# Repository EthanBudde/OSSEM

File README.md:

# OSSEM
OSSEM organization repo

Espresso brewing is a thermo-fluid process where temperature, pressure, flow rate, and time directly effect extraction and flavor. Commercial smart espresso machines offer advanced control, but are expensive, closed-source, and difficult to adapt for experimental research. Existing open-source modifications improve accessibility but do not fully support research-grade measurement or instrumentation. 

This project focuses on building an open-source smart emissions monitor based on the Gaggia Classic Pro, using platforms such as Gaggiuino and Gaggia Mate for embedded control and data logging. The system will allow precise control of brewing parameters, including temperature, pressure, flow profiling, and shot timing. 

Working with the Healthy Buildings Research Lab and the Coffee Telesensing Lab at Portland State University, the machine will be adapted to support PTR-MS and UV-VIS spectroscopy for measuring volatile organic compounds (VOCs) released during espresso extraction. The result will be a flexible, open source platform that supports repeatable espresso brewing and controlled emissions research.

<p align="center">
  <em>Smart Emissions Monitor – Emissions Control Unit (ECU Final Product)</em>
</p>

<p align="center">
  <em>Emissions Control Unit Sensors</em>
</p>

<p align="center">
  <em>Smart Emissions Monitor – Emissions Control Unit (ECU Prototype)</em>
</p>

<p align="center">
  <em>Smart Emissions Monitor – Block Diagram</em>
</p>

<p align="center">
  <em>Smart Emissions Monitor – Schematic v1.8.2</em>
</p>

<p align="center">
  <em>Smart Emissions Monitor – PCB v1.8.2 </em>
</p>

<p align="center">
  <em>Smart Emissions Monitor – 3D PCB v1.8 Front</em>
</p>

<p align="center">
  <em>Smart Emissions Monitor – 3D PCB v1.8 Back</em>
</p>

<p align="center">
  <em>Smart Emissions Monitor – PCB v1.8 front</em>
</p>

<p align="center">
  <em>Smart Emissions Monitor – PCB v1.8 back</em>
</p>

<p align="center">
  <em>Smart Emissions Monitor – PCB v1.8 back with dimensions</em>
</p>

## Acknowledgments
This project builds on:
- Gaggiuino (open-source espresso control system)
- Adafruit sensor libraries
- KiCad component libraries

PCB renders generated using OSH Park

All third-party resources are used in accordance with their respective licenses.

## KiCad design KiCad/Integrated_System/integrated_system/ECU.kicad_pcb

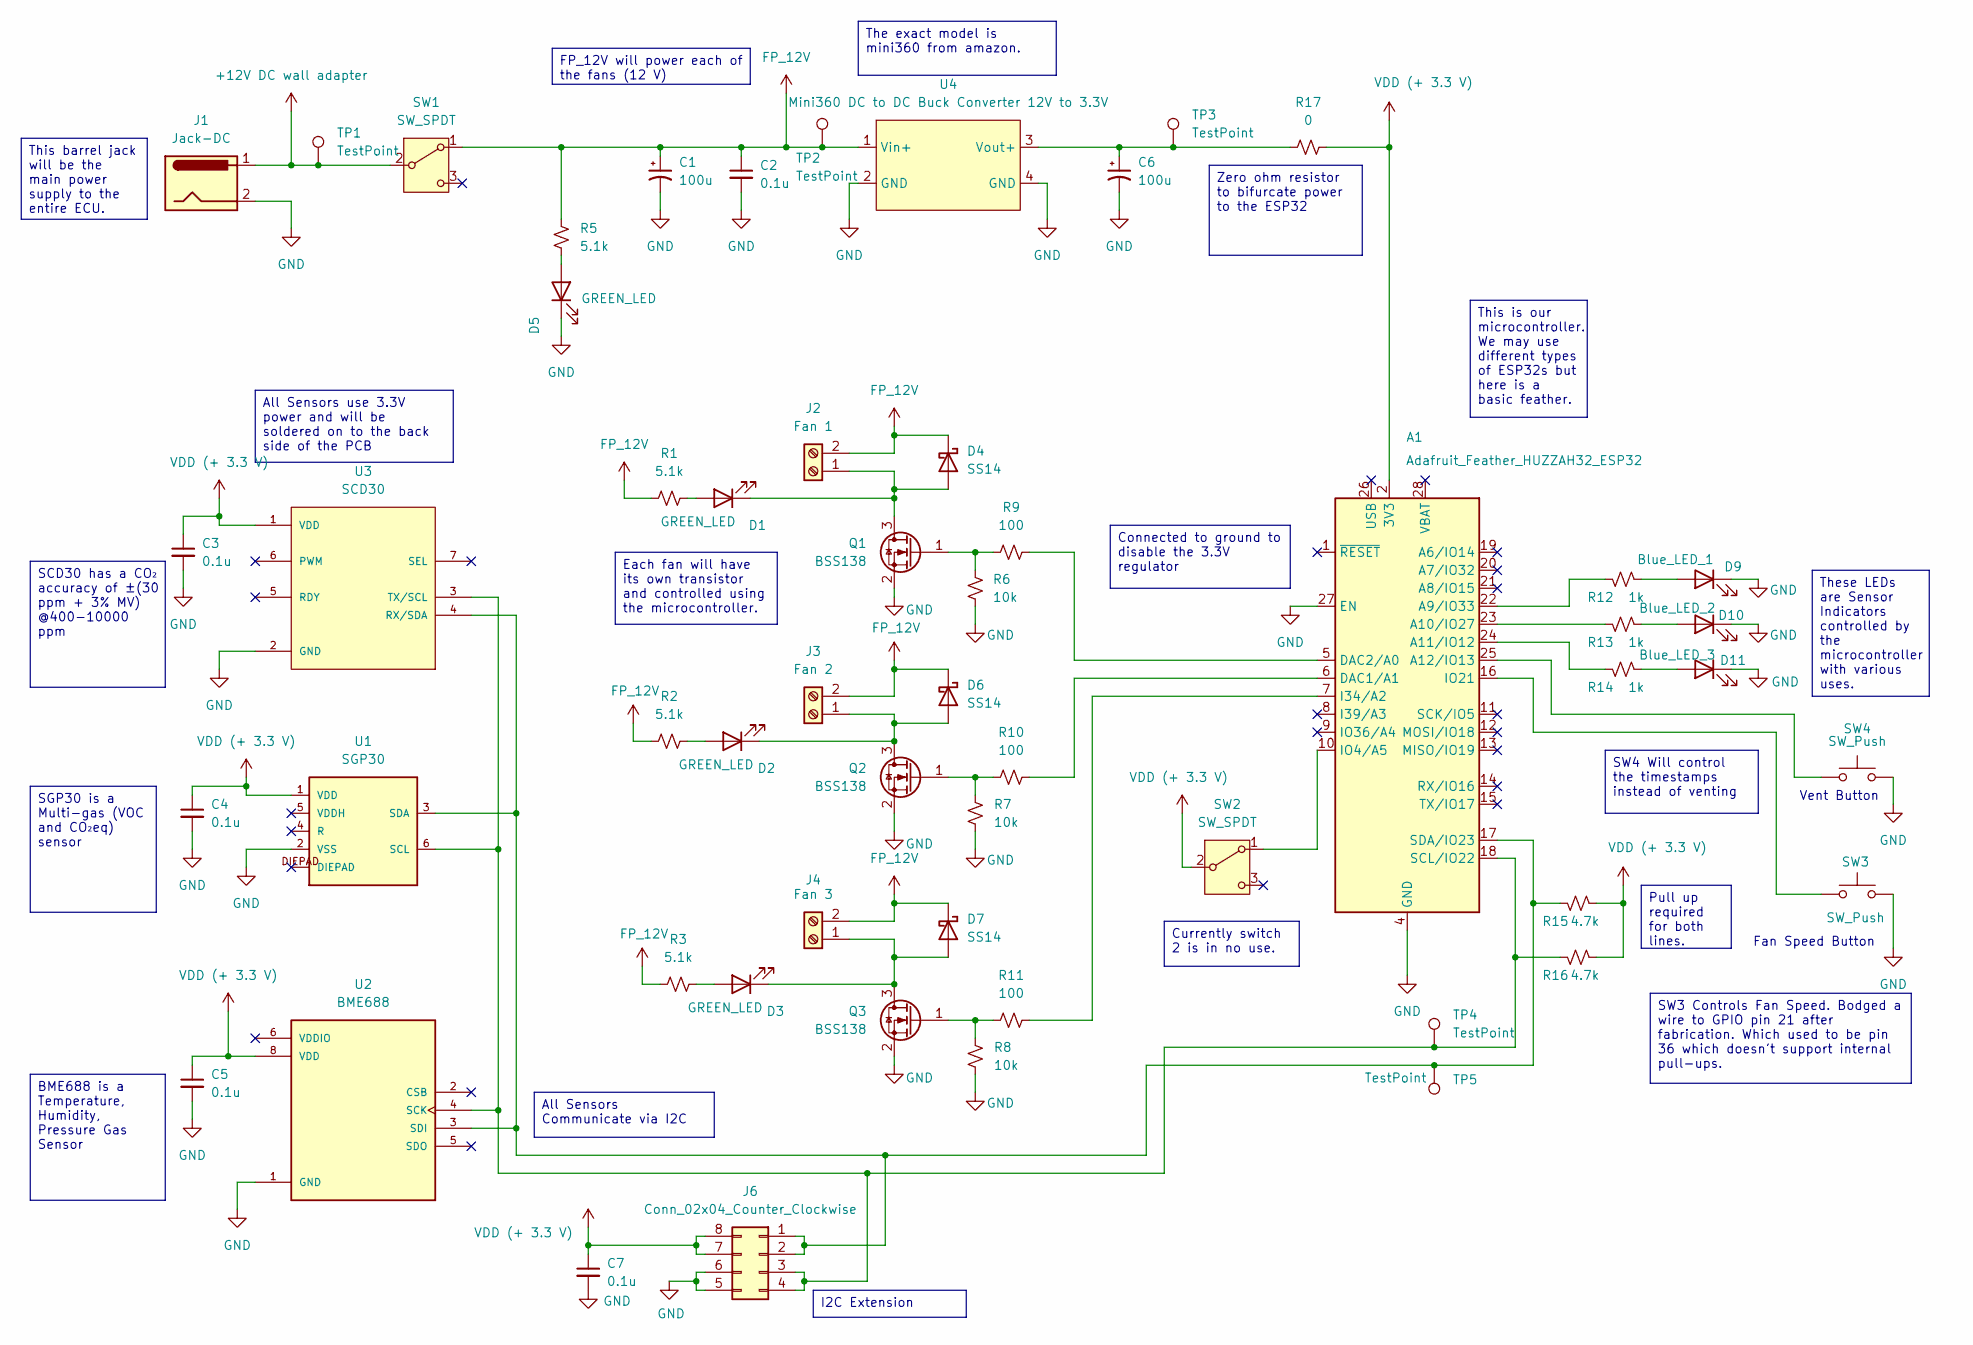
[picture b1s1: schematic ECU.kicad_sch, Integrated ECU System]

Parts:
A1: Adafruit_Feather_HUZZAH32_ESP32; Adafruit_Feather
C1, C6: 100u; CP_Elec_6.3x7.7
C2, C3, C4, C5, C7: 0.1u; C_1206_3216Metric_Pad1.33x1.80mm_HandSolder
D1, D2, D3, D5: GREEN_LED; LED_1206_3216Metric_Pad1.42x1.75mm_HandSolder
D4, D6, D7: SS14; D_SMA
D9: Blue_LED_1; LED_1206_3216Metric_Pad1.42x1.75mm_HandSolder
D10: Blue_LED_2; LED_1206_3216Metric_Pad1.42x1.75mm_HandSolder
D11: Blue_LED_3; LED_1206_3216Metric_Pad1.42x1.75mm_HandSolder
J1: Jack-DC; BarrelJack_GCT_DCJ200-10-A_Horizontal
J2: Fan 1; TerminalBlock_Phoenix_MKDS-1,5-2-5.08_1x02_P5.08mm_Horizont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
J3: Fan 2; TerminalBlock_Phoenix_MKDS-1,5-2-5.08_1x02_P5.08mm_Horizont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
J4: Fan 3; TerminalBlock_Phoenix_MKDS-1,5-2-5.08_1x02_P5.08mm_Horizont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
J6: Conn_02x04_Counter_Clockwise; PinSocket_2x04_P2.54mm_Vertical
Q1, Q2, Q3: BSS138; SOT-23_Handsoldering
R1, R2, R3, R5: 5.1k; R_1206_3216Metric_Pad1.30x1.75mm_HandSolder
R6, R7, R8: 10k; R_1206_3216Metric_Pad1.30x1.75mm_HandSolder
R9, R10, R11: 100; R_1206_3216Metric_Pad1.30x1.75mm_HandSolder
R12, R13, R14: 1k; R_1206_3216Metric_Pad1.30x1.75mm_HandSolder
R15, R16: 4.7k; R_1206_3216Metric_Pad1.30x1.75mm_HandSolder
R17: 0; R_1206_3216Metric_Pad1.30x1.75mm_HandSolder
SW1, SW2: SW_SPDT; switch_dm
SW3, SW4: SW_Push; SW_PUSH_6mm
TP1, TP2, TP3, TP4, TP5: TestPoint; Pin_D0.7mm_L6.5mm_W1.8mm_FlatFork
U1: SGP30
U2: BME688; PSON80P300X300X100-8N; PARTREV 1.9
U3: SCD30; MODULE_SCD30; PARTREV D1
U4: Mini360 DC to DC Buck Converter 12V to 3.3V; Mini360

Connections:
+12V DC wall adapter: J1.1, SW1.2 (B), TP1.1
FP_12V: C1.1, C2.1, D4.1 (K), D6.1 (K), D7.1 (K), J2.2, J3.2, J4.2, R1.1, R2.1, R3.1, R5.2, SW1.1 (A), TP2.1, U4.1 (Vin+)
GND: A1.4 (GND), A1.27 (EN), C1.2, C2.2, C3.2, C4.2, C5.2, C6.2, C7.2, D5.1 (K), D9.1 (K), D10.1 (K), D11.1 (K), J1.2, J6.5, J6.6, Q1.2 (S), Q2.2 (S), Q3.2 (S), R6.1, R7.1, R8.1, SW3.1, SW4.1, U1.2 (VSS), U2.1 (GND), U2.7 (GND), U3.2 (GND), U4.2 (GND), U4.4 (GND)
unnamed: A1.22 (A9/IO33), R12.2
unnamed: A1.23 (A10/IO27), R13.2
unnamed: A1.24 (A11/IO12), R14.2
unnamed: A1.25 (A12/IO13), SW4.2
unnamed: A1.6 (DAC1/A1), R10.2
unnamed: A1.5 (DAC2/A0), R9.2
unnamed: A1.7 (I34/A2), R11.2
unnamed: A1.10 (IO4/A5), SW2.1 (A)
unnamed: A1.16 (IO21), SW3.2
unnamed: A1.18 (SCL/IO22), J6.3, J6.4, R16.2, TP4.1, U1.6 (SCL), U2.4 (SCK), U3.3 (TX/SCL)
unnamed: A1.17 (SDA/IO23), J6.1, J6.2, R15.2, TP5.1, U1.3 (SDA), U2.3 (SDI), U3.4 (RX/SDA)
unnamed: D1.2 (A), R1.2
unnamed: D1.1 (K), D4.2 (A), J2.1, Q1.3 (D)
unnamed: D2.2 (A), R2.2
unnamed: D2.1 (K), D6.2 (A), J3.1, Q2.3 (D)
unnamed: D3.2 (A), R3.2
unnamed: D3.1 (K), D7.2 (A), J4.1, Q3.3 (D)
unnamed: D5.2 (A), R5.1
unnamed: D9.2 (A), R12.1
unnamed: D10.2 (A), R13.1
unnamed: D11.2 (A), R14.1
unnamed: Q1.1 (G), R6.2, R9.1
unnamed: Q2.1 (G), R7.2, R10.1
unnamed: Q3.1 (G), R8.2, R11.1
unnamed: C6.1, R17.1, TP3.1, U4.3 (Vout+)
VDD (+ 3.3 V): A1.2 (3V3), C3.1, C4.1, C5.1, C7.1, J6.7, J6.8, R15.1, R16.1, R17.2, SW2.2 (B), U1.1 (VDD), U2.8 (VDD), U3.1 (VDD)

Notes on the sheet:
Vent Button
Fan Speed Button
These LEDs are Sensor Indicators controlled by the microcontroller with various uses.
Each fan will have its own transistor and controlled using the microcontroller.
Connected to ground to disable the 3.3V regulator
BME688 is a Temperature, Humidity, Pressure Gas Sensor
I2C Extension
SGP30 is a Multi-gas (VOC and CO₂eq) sensor
SW3 Controls Fan Speed. Bodged a wire to GPIO pin 21 after fabrication. Which used to be pin 36 which doesn't support internal pull-ups.
FP_12V will power each of the fans (12 V)
Zero ohm resistor to bifurcate power to the ESP32
The exact model is mini360 from amazon.
All Sensors use 3.3V power and will be soldered on to the back side of the PCB
All Sensors Communicate via I2C
SCD30 has a CO₂ accuracy of ±(30 ppm + 3% MV) @400-10000 ppm
This barrel jack will be the main power supply to the entire ECU.
This is our microcontroller. We may use different types of ESP32s but here is a basic feather.
Currently switch 2 is in no use.
SW4 Will control the timestamps instead of venting
Pull up required for both lines.

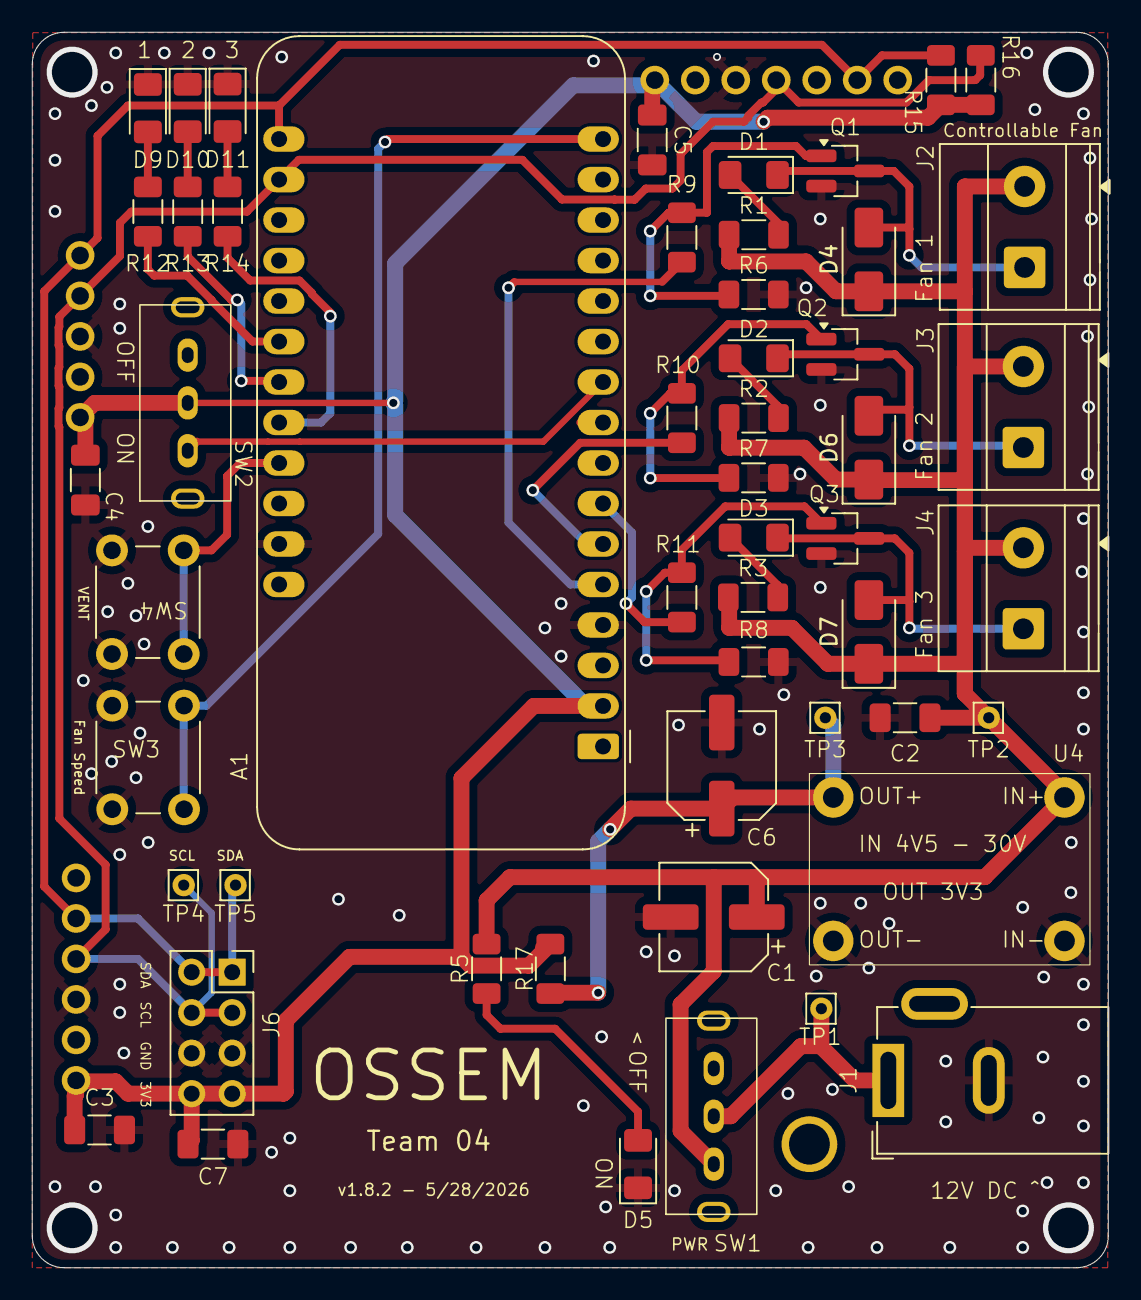
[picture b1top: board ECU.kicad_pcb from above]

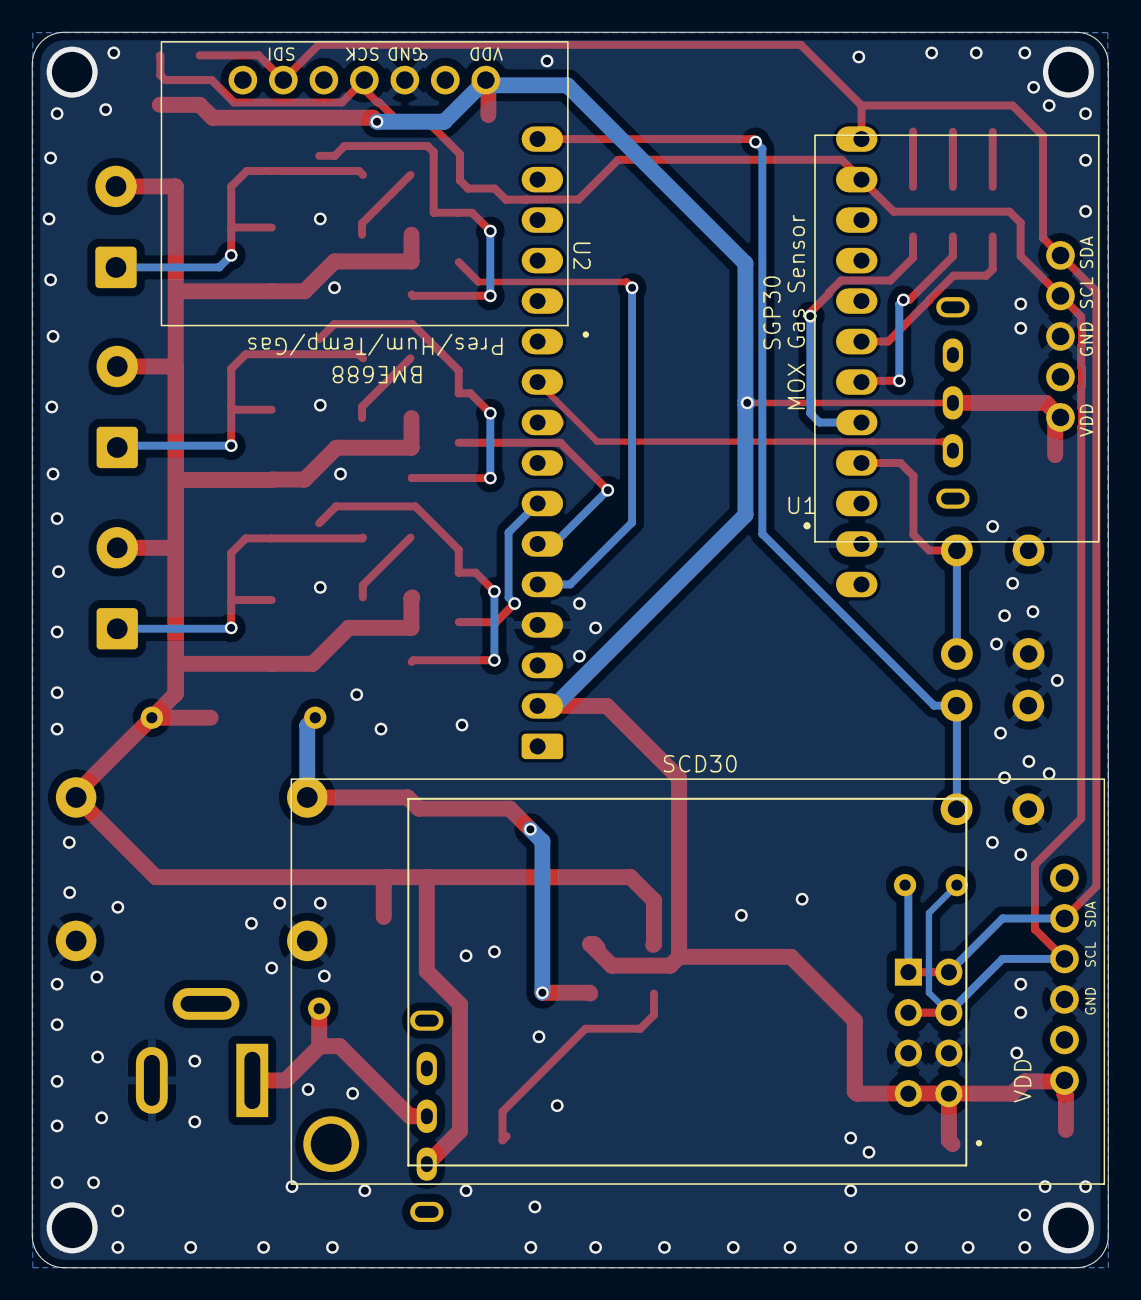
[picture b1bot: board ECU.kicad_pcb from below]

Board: 2 copper layers, 67.5 x 77.5 mm, 55 parts (3 on the bottom side), 29 nets.

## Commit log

2026-02-28 Fan Control KiCad Files
2026-02-28 Renamed the title
2026-02-28 Replaced LR7843 footprint
2026-02-28 Rev1.1 with new symbol
    Kicad did a funny thing and decided to update its symbols and pinouts
2026-02-28 Centered the circuit
2026-04-04 New Project
    Made a new project folder for the integrated system for the ECU
2026-04-04 Added Components
    Added esp32 and some transistors
2026-04-09 Added Sensors
    Made a bunch of changes
2026-04-09 Added Notes
2026-04-09 changed to bme280
2026-04-09 replaced transistors
2026-04-11 Renamecomp
2026-04-13 Replaced with bme680 sensor
2026-04-13 Added LEDs
2026-04-14 Fixed LED placement
    LED Placement and added switch
2026-04-14 Switched to the right pins
2026-04-14 Added no connects
2026-04-15 rev 1.1
2026-04-16 changed ground
2026-04-20 Updated LED schematic
2026-04-20 Updated the descriptions
2026-04-21 Folder Managment
2026-04-21 Notes
2026-04-21 test
2026-04-21 Updated Footprint v1.1
2026-04-21 Started PCB layout
2026-04-21 Updated Footprints v1.2
2026-04-21 Updated Footpirnt libraries v1.3
2026-04-21 PCB Layout started v1.1
2026-04-21 Layout rev 1.2
2026-04-21 quick changes
2026-04-21 changes made
2026-04-21 changed wire
2026-04-22 changed
2026-04-22 Replaced the transistors to BSS138
    BSS138 is SMD type
2026-04-22 Changed the net for buck
2026-04-22 Rough Board layout
2026-04-23 made changes
2026-04-23 SGP30 & BME680 Foot print edit
    Made a ton of changes
2026-04-23 Nets Label
2026-04-23 redesign v1.3
2026-04-23 Layout Complete
2026-04-23 Changed 3d model of esp32
2026-04-23 3d renderings
2026-04-23 v1 Routing
2026-04-23 parser commit
2026-04-24 datasets and example
2026-04-24 deleted all traces
2026-04-24 deleted pot
2026-04-24 added zero ojm resistors and testpoints
2026-04-24 added I2C extension
2026-04-24 redesign
2026-04-24 small adjustments
2026-04-24 title
2026-04-24 initial routing started
2026-04-24 Routing Complete
2026-04-24 added copper ground layers
2026-04-24 headers
2026-04-25 added a ton of vias
2026-04-25 forgot to route some pins
2026-04-25 rev1.5
2026-04-25 Fixed DRC Errors
    One left we need to figure out how to fix it
2026-04-26 Added via
2026-04-27 burnin commit
2026-04-27 moved for arduino purposes
2026-04-28 burnin update wip
2026-04-28 burnin main refactor
2026-04-29 1.6 rev
2026-04-29 Routing rev1.6 complete
2026-04-29 1.6 done
2026-04-29 ran drc
2026-04-29 added images
2026-04-29 added html img
2026-04-29 fixed png
2026-04-29 text edit
2026-04-29 operation changes
2026-04-29 updating comments
2026-04-29 parser comments, dummy file.txt
    file.txt derived from examples, not great data
2026-04-29 updated to reflect burnin changes, more active data tracking
2026-04-29 fix missing data
2026-04-30 dataset reorder/dir update
2026-05-01 Rerouted version 1.7
2026-05-01 edits
2026-05-01 readme
2026-05-01 added ground planes
2026-05-01 added dimensions
2026-05-02 fixed a lot of the issues brought up from design review
2026-05-02 design review fixes
2026-05-02 last checks
2026-05-02 uploaded to oshpark
2026-05-03 dimensions added for ME team
2026-05-03 removed dimensions
2026-05-03 updated pictures
2026-05-03 updated captions
2026-05-04 img updated
2026-05-04 acknowledgements
2026-05-04 osh park renders
2026-05-07 Three modes to control fan speed
2026-05-07 5_1ptrms1
2026-05-08 fan speed / (manual) shot shading wip
2026-05-08 shading wip
2026-05-12 comments, timerflag function change
2026-05-20 changed led
2026-05-25 etc ecu stuff
2026-05-25 gitignore
2026-05-25 wip new functionalization
2026-05-25 ecu compartmentalization
2026-05-26 deleted altium folder
2026-05-26 Updated ecu_main with button functionality
2026-05-26 updated ecu code w/ custom hotspot variables
2026-05-28 etc script reorganization
2026-05-28 5_29 datasets
2026-05-28 parser->plotter_old
2026-05-28 new plotter work, worker files
2026-05-28 img added
2026-05-29 updated button2 to pin 21
2026-05-29 edited schematic to v1.8.2
    fixed the schematic and layout routing of sw3 gpio 36 to gpio21
2026-05-29 Updated Readme imgs
2026-05-29 changed to ossem
2026-05-29 changed the figures
2026-06-04 button, trigger fixes
2026-06-08 gaggiuino full schematic
2026-06-08 added block diagram
2026-06-11 Update project focus to smart emissions monitor
2026-06-11 Uploaded documentation
2026-06-11 more files uploaded
2026-06-11 deleted repeated files
2026-06-13 standup
2026-06-13 pushed
2026-06-13 comments
